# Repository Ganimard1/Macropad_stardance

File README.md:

# Mcrpd
This is a rather elementary macropad featuring 3 keys, a rotary encoder, an OLED screen, and 4 leds with QMK based firmware and via support. It's my first hardware project ever and is designed as a submission for the Hackpad V5 as part of the stardance challenge. The keys on either end play the previous and next media and the middle one is just alt+tab. The rotary encoder controls system volume and the LEDs and OLED screen are for asthetic purposes. I do want to mention here, since this is my first hardware project and I've no prior experience with hardware some AI was used to help me navigate new and unfamiliar tools such as kicad.

## PCB & Schematic
The PCB includes a mounting hole that isn't actually a mounting hole. I thought that would be pretty funny(Kicanvas link: https://kicanvas.org/?repo=https%3A%2F%2Fgithub.com%2FGanimard1%2FMcrpd_stardance%2Ftree%2Fmain%2FPCB) . I had to reroute this like 30 times and am really proud of how it turned out (0 DRC errors FINALLY):

### Case
I didn't want to obscure most of the macropad and wanted the PCB to show so I ended up with this design. The little rectangle above the MCU is a little shroud thing I added and is to be glued on after the PCB is placed inside the case:

#### BOM:
1x Seeed XIAO RP2040

4x SK 6182 mini-e LEDs

1x EC11E rotary encoder

1x 0.91 inch OLED display(128x32)

3x keycaps

3x MX-type switches or equivalent

4x M3x16mm screws

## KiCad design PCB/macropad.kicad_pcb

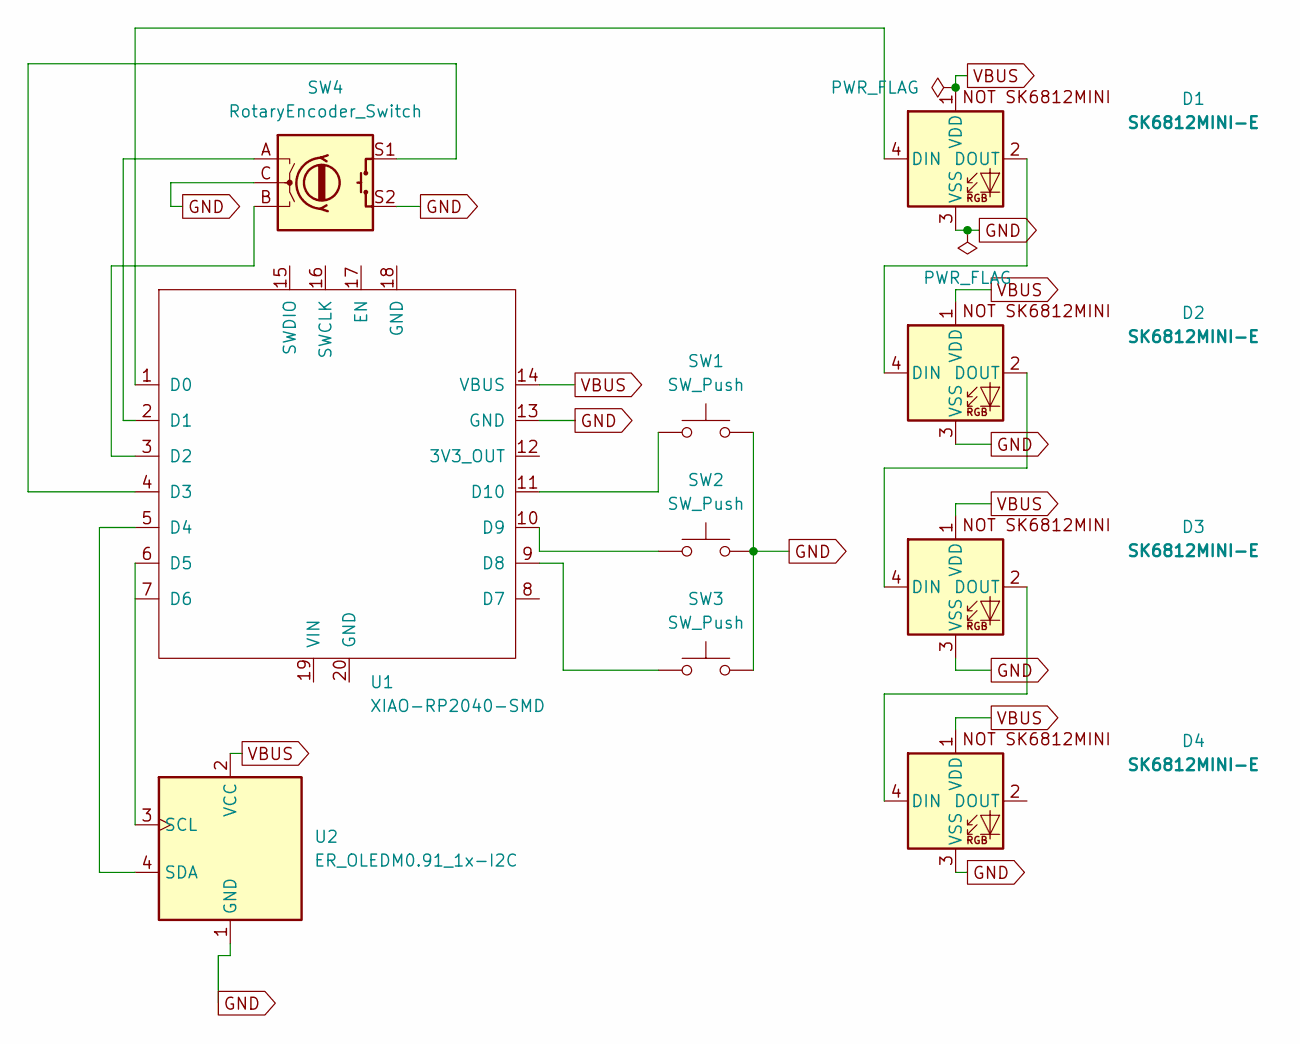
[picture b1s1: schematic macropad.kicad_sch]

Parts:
D1, D2, D3, D4: SK6812MINI-E; SK6812MINI-E_fixed
SW1, SW2, SW3: SW_Push; SW_Cherry_MX_1.00u_PCB
SW4: RotaryEncoder_Switch; RotaryEncoder_Alps_EC11E-Switch_Vertical_H20mm
U1: XIAO-RP2040-SMD
U2: ER_OLEDM0.91_1x-I2C

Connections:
GND: D1.3 (VSS), D2.3 (VSS), D3.3 (VSS), D4.3 (VSS), SW1.2, SW2.2, SW3.2, SW4.C, SW4.S2, U1.13 (GND), U2.1 (GND)
unnamed: D1.4 (DIN), U1.1 (D0)
unnamed: D1.2 (DOUT), D2.4 (DIN)
unnamed: D2.2 (DOUT), D3.4 (DIN)
unnamed: D3.2 (DOUT), D4.4 (DIN)
unnamed: SW4.A, U1.2 (D1)
unnamed: SW4.B, U1.3 (D2)
unnamed: SW4.S1, U1.4 (D3)
unnamed: U1.5 (D4), U2.4 (SDA)
unnamed: U1.6 (D5), U2.3 (SCL)
unnamed: SW3.1, U1.9 (D8)
unnamed: SW2.1, U1.10 (D9)
unnamed: SW1.1, U1.11 (D10)
VBUS: D1.1 (VDD), D2.1 (VDD), D3.1 (VDD), D4.1 (VDD), U1.14 (VBUS), U2.2 (VCC)

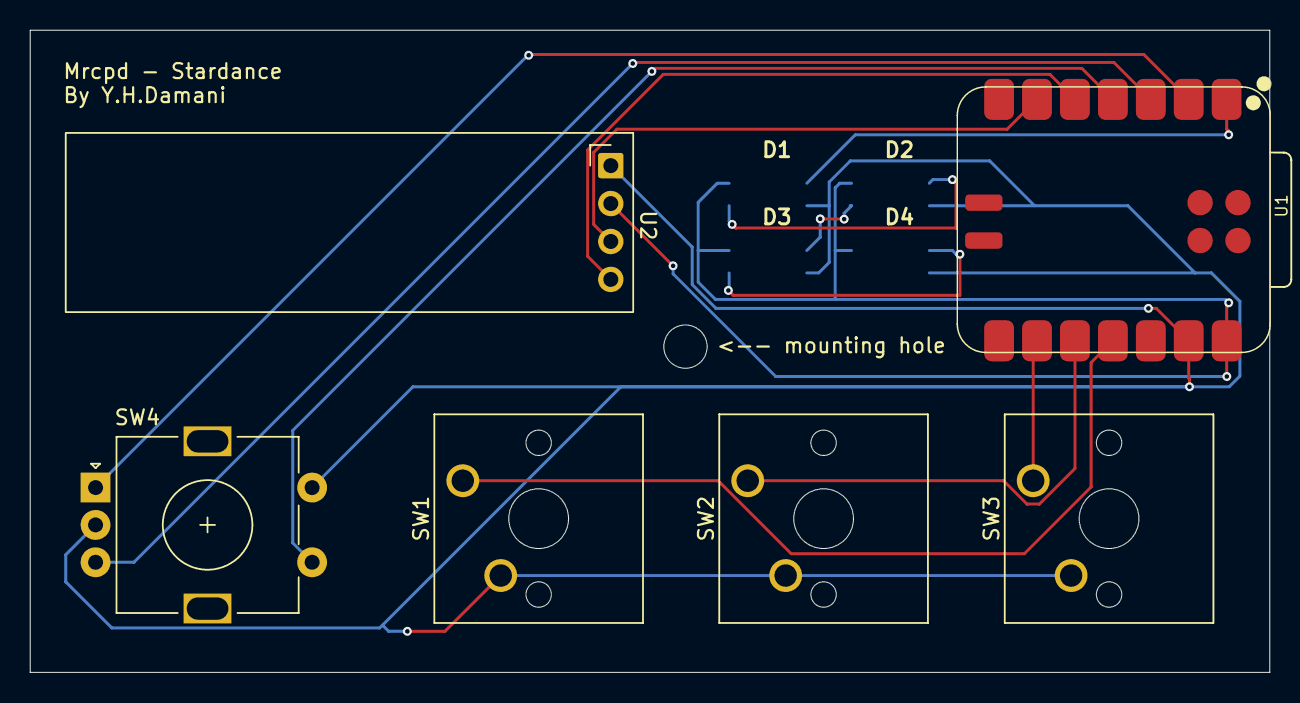
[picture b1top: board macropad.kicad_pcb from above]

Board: 2 copper layers, 83.0 x 43.0 mm, 10 parts (0 on the bottom side), 14 nets.
